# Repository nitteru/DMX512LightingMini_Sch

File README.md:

# DMX512LightingMini_Sch
Compact LED illumination that can be dimmed by DMX 512.

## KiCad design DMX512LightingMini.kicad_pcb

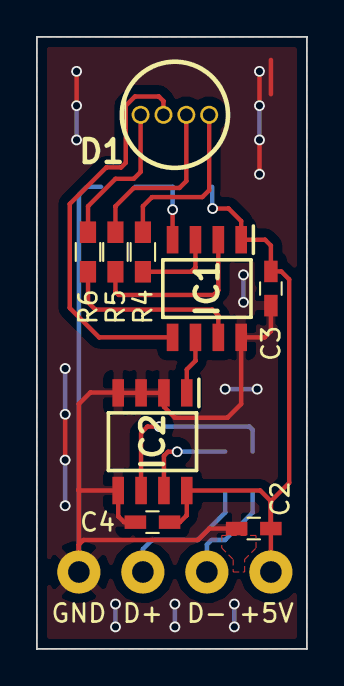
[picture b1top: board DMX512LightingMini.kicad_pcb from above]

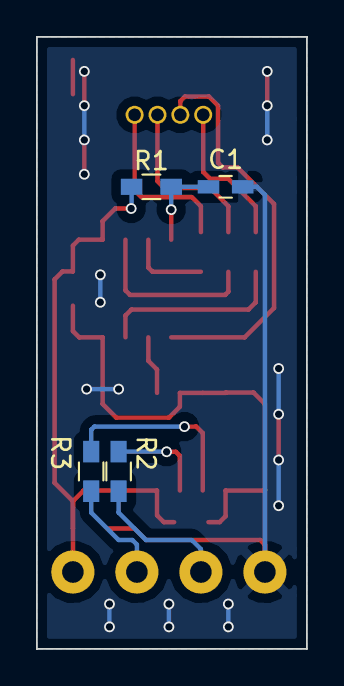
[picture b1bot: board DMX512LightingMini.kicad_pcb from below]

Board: 2 copper layers, 15.0 x 34.0 mm, 17 parts (4 on the bottom side), 15 nets.

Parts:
+5V: +5V; SolderWirePad_single_1-2mmDrill
C1, C3, C4: 0.1u; C_0603_HandSoldering
C2: 1u; C_0603_HandSoldering
D1: L-154A4SURKQBDZGW; KNIGHTBRIGHT-1.27PITCH-4PIN
D+: DATA+; SolderWirePad_single_1-2mmDrill
D-: DATA-; SolderWirePad_single_1-2mmDrill
GND: GND; SolderWirePad_single_1-2mmDrill
IC1: PIC12F1840-I_SN; SOIC127P600X175-8N
IC2: ADM4852ARZ; SOIC127P600X175-8N
R1: 10k; R_0603_HandSoldering
R2, R3: 100; R_0603_HandSoldering
R4, R5, R6: 330; R_0603_HandSoldering

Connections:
+5V: +5V.1, C2.1, C3.1, C4.1, IC1.1, IC2.8, R1.1
DATA+: IC2.7, R2.2
DATA-: IC2.6, R3.2
GND: C1.2, C2.2, C3.2, C4.2, GND.1, IC1.8, IC2.2, IC2.3, IC2.4, IC2.5
unnamed: C1.1, IC1.4, R1.2
unnamed: D1.1, R6.2
unnamed: D1.2, IC1.5
unnamed: D1.3, R5.1
unnamed: D1.4, R4.2
unnamed: IC1.2, R5.2
unnamed: IC1.3, R4.1
unnamed: IC1.6, IC2.1
unnamed: IC1.7, R6.1
unnamed: D+.1, R2.1
unnamed: D-.1, R3.1

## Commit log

2017-08-22 * First Commit * プロジェクト作成
2017-08-22 * 部品配置開始
2017-09-25 * 回路図をほぼ固めた * アートワーク開始
2017-09-30 * AW作業中
2017-09-30 * アートワーク作業中
2018-05-05 * アートワーク完了 * 四角版
